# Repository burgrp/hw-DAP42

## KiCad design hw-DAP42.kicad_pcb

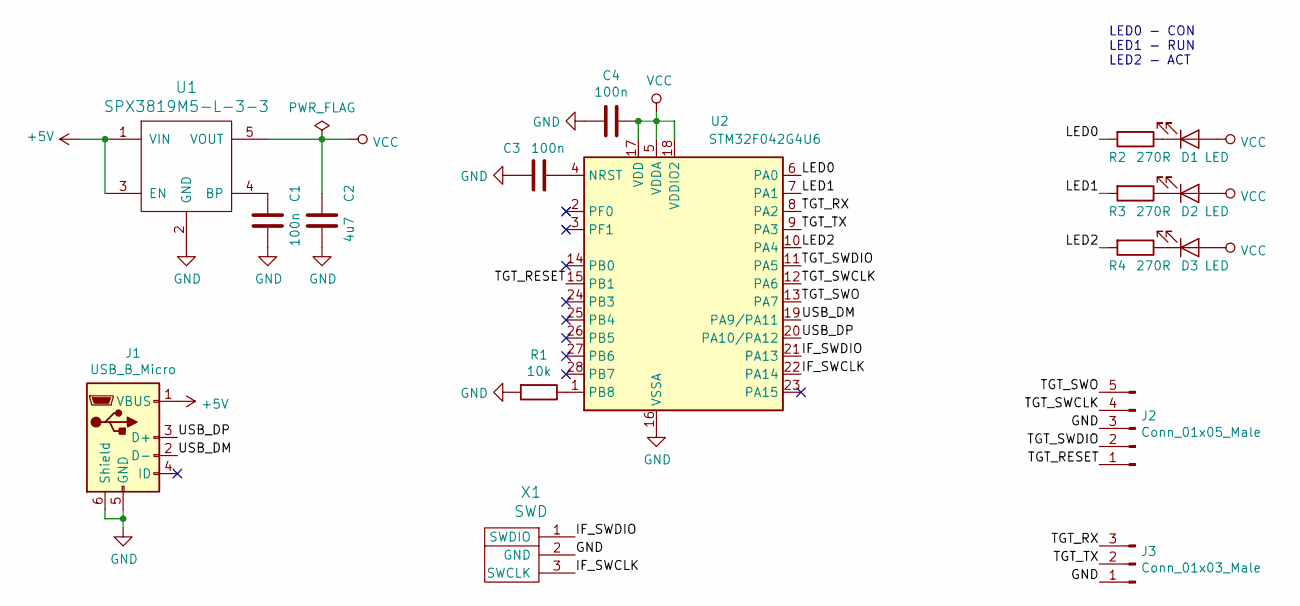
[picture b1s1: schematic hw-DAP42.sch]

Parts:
C1, C3, C4: 100n; C_0805_2012Metric
C2: 4u7; C_0805_2012Metric
D1, D2, D3: LED; LED_0805_2012Metric_Pad1.15x1.40mm_HandSolder
J1: USB_B_Micro; conn_usb_B_micro_smd-2
J2: Conn_01x05_Male; PinHeader_1x05_P2.54mm_Vertical
J3: Conn_01x03_Male; PinHeader_1x03_P2.54mm_Vertical
R1: 10k; R_0805_2012Metric
R2, R3, R4: 270R; R_0805_2012Metric
U1: SPX3819M5-L-3-3; SOT-23-5_HandSoldering
U2: STM32F042G4U6; QFN-28_4x4mm_P0.5mm
X1: SWD

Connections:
+5V: J1.1 (VBUS), U1.1 (VIN), U1.3 (EN)
/IF_SWCLK: U2.22 (PA14), X1.3 (SWCLK)
/IF_SWDIO: U2.21 (PA13), X1.1 (SWDIO)
/LED0: R2.2, U2.6 (PA0)
/LED1: R3.2, U2.7 (PA1)
/LED2: R4.2, U2.10 (PA4)
/TGT_RESET: J2.1, U2.15 (PB1)
/TGT_RX: J3.3, U2.8 (PA2)
/TGT_SWCLK: J2.4, U2.12 (PA6)
/TGT_SWDIO: J2.2, U2.11 (PA5)
/TGT_SWO: J2.5, U2.13 (PA7)
/TGT_TX: J3.2, U2.9 (PA3)
/USB_DM: J1.2 (D-), U2.19 (PA9/PA11)
/USB_DP: J1.3 (D+), U2.20 (PA10/PA12)
GND: C1.1, C2.1, C3.2, C4.2, J1.5 (GND), J1.6 (Shield), J2.3, J3.1, R1.2, U1.2 (GND), U2.16 (VSSA), X1.2 (GND)
unnamed: C1.2, U1.4 (BP)
unnamed: C3.1, U2.4 (NRST)
unnamed: D1.1 (K), R2.1
unnamed: D2.1 (K), R3.1
unnamed: D3.1 (K), R4.1
unnamed: R1.1, U2.1 (PB8)
VCC: C2.2, C4.1, D1.2 (A), D2.2 (A), D3.2 (A), U1.5 (VOUT), U2.5 (VDDA), U2.17 (VDD), U2.18 (VDDIO2)

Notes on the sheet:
LED0 - CON LED1 - RUN LED2 - ACT

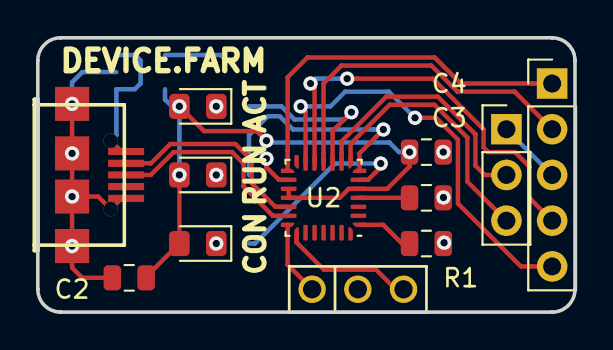
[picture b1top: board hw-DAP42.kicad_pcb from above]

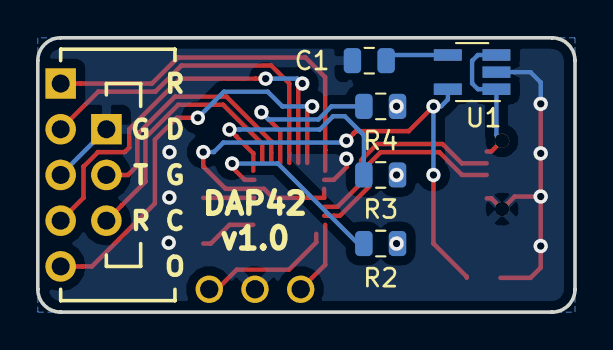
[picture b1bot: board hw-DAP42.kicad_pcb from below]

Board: 2 copper layers, 29.8 x 15.2 mm, 17 parts (5 on the bottom side), 22 nets.
